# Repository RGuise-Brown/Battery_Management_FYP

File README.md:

# Battery Monitoring System for Lithium Thionyl Chloride Batteries

A battery monitoring system designed to track the health and state of charge of lithium thionyl chloride batteries operating in extreme cold conditions in the Southern Ocean Marginal Ice Zone (SO MIZ).

## Project Overview

This project was completed as a final year project (EEE4022S) for a Mechatronics Engineering degree at the University of Cape Town (UCT) in 2025.

**Author**: Rachael Guise-Brown  
**Supervisor**: Robyn Verrinder  
**Institution**: University of Cape Town

## Application

This battery monitoring system was designed for the **SHARC (Southern Hemisphere Antarctic Research Collective) Buoy**, which operates in the Southern Ocean Marginal Ice Zone. The system focuses on monitoring battery health in extreme cold conditions and adjusts the expected state of charge based on temperature changes.

## Battery Technology

Lithium thionyl chloride (Li-SOCl₂) batteries present unique monitoring challenges:
- **Primary battery** (non-rechargeable)
- **Very flat voltage discharge curve** - voltage alone is insufficient for accurate SOC estimation
- **Temperature-dependent performance** - capacity varies significantly with temperature

Due to these characteristics, the system uses **coulomb counting** and other methods to estimate state of charge, particularly important in the cold operating conditions of the Southern Ocean.

## System Features

### Hardware
- **INA226 Power Monitor**: Fully implemented and calibrated for accurate current and power measurement
- **BQ35100 Fuel Gauge**: Partial implementation but challenges with calibration and configuration without evaluation module (EVM)
- **Temperature Monitoring**: Three sensors tested
  - TMP117 digital I2C sensor
  - TMP36 (TO-92) analog sensor
  - TMP36 with shutdown (SOT-23) analog sensor (chosen sensor)
- **STM32 Nucleo-L4R5ZI**: Main microcontroller platform

### Firmware
- Real-time current, voltage, and capacity monitoring
- Temperature-compensated state of charge estimation
- Multiple algorithm implementations for data analysis
- I2C communication with all sensors
- Support for BQ35100 mode switching (EOS/ACC)
- Discharge cycle testing capabilities

## Repository Structure

```
├── firmware/          # Embedded C code for STM32
├── hardware/          # KiCad PCB designs and schematics
└── docs/              # Datasheets and reference documentation
```

## Implementation Status

### Fully Implemented ✓
- INA226 power monitor with calibration
- Temperature sensor array (TMP117, TMP36 sensors)
- BQ35100 basic functionality:
  - Current, voltage, and capacity reading
  - Mode switching (EOS ↔ ACC)
  - EOS impedance measurements (uncalibrated)
- Real-time monitoring algorithms
- Temperature-compensated SOC estimation

### Known Limitations
- BQ35100 I2C calibration is not functional through firmware

## Getting Started

### Hardware Setup
1. Review the hardware designs in `/hardware`
2. Assemble or obtain the custom PCBs:
   - BQ35100 fuel gauge board
   - Temperature sensor board
   - STM32 Nucleo Hat with INA226
3. Connect boards to STM32 Nucleo-L4R5ZI

### Firmware Setup
1. Navigate to `/firmware` directory
2. Build and flash the firmware to the STM32 Nucleo-L4R5ZI
3. Configure parameters as needed for your battery specifications

### Documentation
Refer to `/docs` for component datasheets and reference materials.

## Key Technologies

- **Microcontroller**: STM32L4R5ZI (ARM Cortex-M4)
- **Development Environment**: ARM GCC toolchain, STM32CubeIDE
- **Hardware Design**: KiCad
- **Communication Protocols**: I2C, UART
- **Programming Language**: C

## License

This project is licensed under the MIT License - see the LICENSE file for details.

## Acknowledgments

- **Robyn Verrinder** - Project supervisor
- **University of Cape Town** - Department of Electrical Engineering
- **SHARC Project** - Application context and requirements
- **Texas Instruments** - BQ35100 and INA226 reference designs

## Contact

Rachael Guise-Brown  
University of Cape Town  
2025

---

*Final Year Project (EEE4022S) - Mechatronics Engineering*  
*University of Cape Town*

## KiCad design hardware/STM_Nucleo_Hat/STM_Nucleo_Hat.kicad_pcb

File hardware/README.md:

# Hardware Documentation

Hardware design files for the Battery Monitoring System, including custom PCB designs created in KiCad.

## Overview

Three main PCB designs that integrate with an STM32 Nucleo-L4R5ZI development board to create a complete battery monitoring solution.

## PCB Designs

### 1. STM32 Nucleo Hat (STM_Nucleo_Hat)
Board borrowed from ARU that contains INA226 power monitor which is the only component used in this project.

**Files**: Located in `/STM_Nucleo_Hat/` directory

---

### 2. BQ35100 Board (FYP_PMIC)
Custom board featuring the Texas Instruments BQ35100 fuel gauge for battery monitoring.

**Files**: Located in `/FYP_PMIC/` directory

---

### 3. Temperature Sensor Board (FYP_temp)
Custom board with three temperature sensors:
- TMP117 (digital I2C sensor)
- TMP36 (TO-92 analog sensor)
- TMP36 with shutdown (SOT-23 analog sensor)

**Files**: Located in `/FYP_temp/` directory

---

## Schematics

Full schematics are provided in both PDF and image formats for easy viewing:

### BQ35100 Board
- `BQ35100 Schematic.pdf` - Full schematic documentation
- `BQ35100 Schematic.png` - Quick reference image

### INA226 Board
- `INA226 Full Board Schematic.pdf` - Complete board schematic
- `INA226 Schematic.jpeg` - Quick reference image

### Temperature Sensor Board
- `Temp Board Schematic.pdf` - Full schematic documentation
- `Temp Schematic.png` - Quick reference image

## KiCad Component Files

Custom component libraries and footprints are located in the `/KiCad component files/` directory. These include:
- Custom symbols for BQ35100, INA226, and temperature sensors

## Design Tools

**Software**: KiCad 6.0 or later

## Getting Started

Open the `.kicad_pro` file in the respective board directory, or view the PDF schematics directly.

## Component Information

**Key ICs Used**:
- INA226 power monitor (on STM Nucleo Hat)
- BQ35100 fuel gauge
- TMP117 digital temperature sensor
- TMP36 analog temperature sensors (x2)

**Microcontroller**: STM32 Nucleo-L4R5ZI development board

## Notes

- INA226 is fully implemented and calibrated
- BQ35100 has partial implementation (see firmware README for details)
- All designs created in KiCad

---

For firmware documentation, see the main repository README.

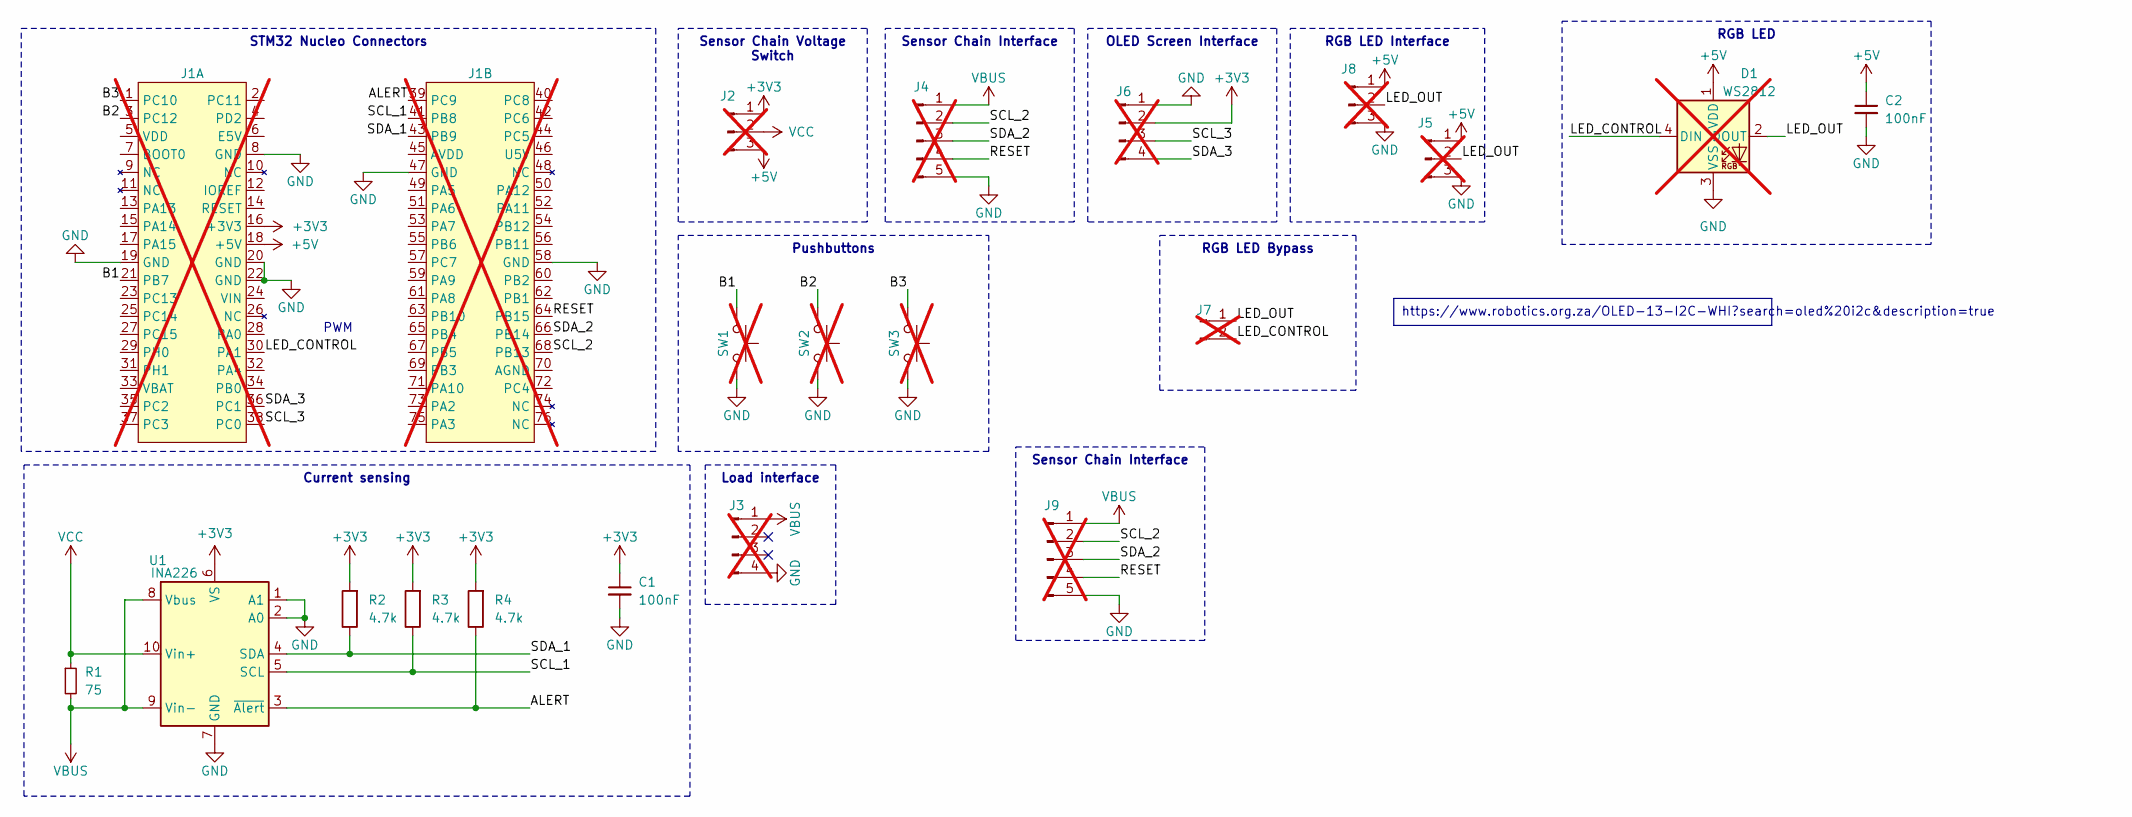
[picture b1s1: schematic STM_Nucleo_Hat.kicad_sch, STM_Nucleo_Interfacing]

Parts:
C1, C2: 100nF; C_0603_1608Metric; LCSC C14663
D1: WS2812; LED_WS2812B_PLCC4_5.0x5.0mm_P3.2mm; LCSC C2843785; not fitted
J1: Nucleo64-Pins; not fitted
J2, J5, J8: Conn_01x03_Pin; PinHeader_1x03_P2.54mm_Vertical; not fitted
J3: Conn_01x05_Pin; PinHeader_1x04_P2.54mm_Vertical; not fitted
J4, J9: Conn_01x05_Pin; PinHeader_1x05_P2.54mm_Vertical; not fitted
J6: Conn_01x05_Pin; 1.3_OLED_Screen; not fitted
J7: Conn_01x02_Pin; PinHeader_1x02_P2.54mm_Vertical; not fitted
R1: 75; C_0805_2012Metric_Pad1.18x1.45mm_HandSolder; LCSC C3033913
R2, R3, R4: 4.7k; R_0603_1608Metric; LCSC C23162
SW1, SW2, SW3: SW_Push; SW_PUSH_6mm; not fitted
U1: INA226; MSOP-10_3x3mm_P0.5mm; LCSC C49851

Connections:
+3V3: C1.1, J1.16 (+3V3), J2.1, J6.2, R2.2, R3.2, R4.2, U1.6 (VS)
+5V: C2.1, D1.1 (VDD), J1.18 (+5V), J2.3, J5.1, J8.1
/ALERT: J1.39 (PC9), R4.1, U1.3 (~Alert)
/B1: J1.21 (PB7), SW1.1
/B2: J1.3 (PC12), SW2.1
/B3: J1.1 (PC10), SW3.1
/LED_CONTROL: D1.4 (DIN), J1.30 (PA1), J7.2
/LED_OUT: D1.2 (DOUT), J5.2, J7.1, J8.2
/RESET: J1.64 (PB15), J4.4, J9.4
/SCL_1: J1.41 (PB8), R3.1, U1.5 (SCL)
/SCL_2: J1.68 (PB13), J4.2, J9.2
/SCL_3: J1.38 (PC0), J6.3
/SDA_1: J1.43 (PB9), R2.1, U1.4 (SDA)
/SDA_2: J1.66 (PB14), J4.3, J9.3
/SDA_3: J1.36 (PC1), J6.4
GND: C1.2, C2.2, D1.3 (VSS), J1.8 (GND), J1.19 (GND), J1.20 (GND), J1.22 (GND), J1.47 (GND), J1.58 (GND), J3.4, J4.5, J5.3, J6.1, J8.3, J9.5, SW1.2, SW2.2, SW3.2, U1.1 (A1), U1.2 (A0), U1.7 (GND)
VBUS: J3.1, J4.1, J9.1, R1.2, U1.8 (Vbus), U1.9 (Vin-)
VCC: J2.2, R1.1, U1.10 (Vin+)

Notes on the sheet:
Sensor Chain Interface
RGB LED
Pushbuttons
https://www.robotics.org.za/OLED-13-I2C-WHI?search=oled%20i2c&description=true
STM32 Nucleo Connectors
RGB LED Interface
Load interface
Current sensing
OLED Screen Interface
RGB LED Bypass
Sensor Chain Voltage Switch
PWM

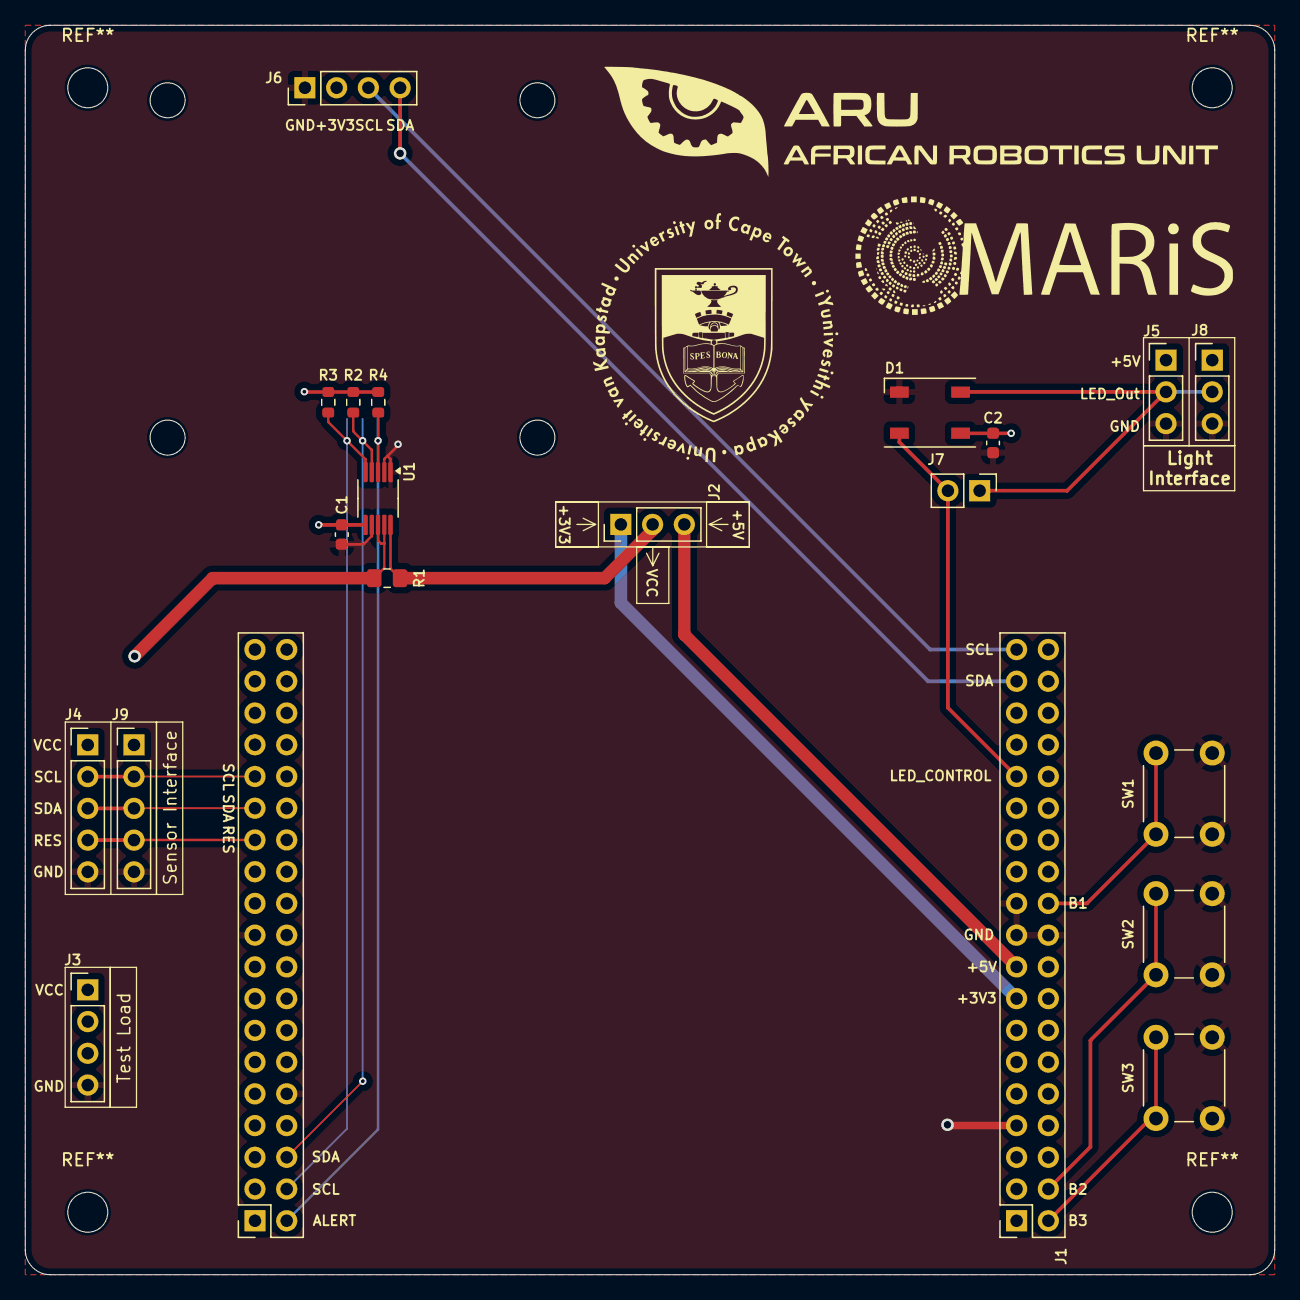
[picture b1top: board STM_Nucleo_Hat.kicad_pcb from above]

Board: 4 copper layers, 100.0 x 100.0 mm, 20 parts (0 on the bottom side), 18 nets.

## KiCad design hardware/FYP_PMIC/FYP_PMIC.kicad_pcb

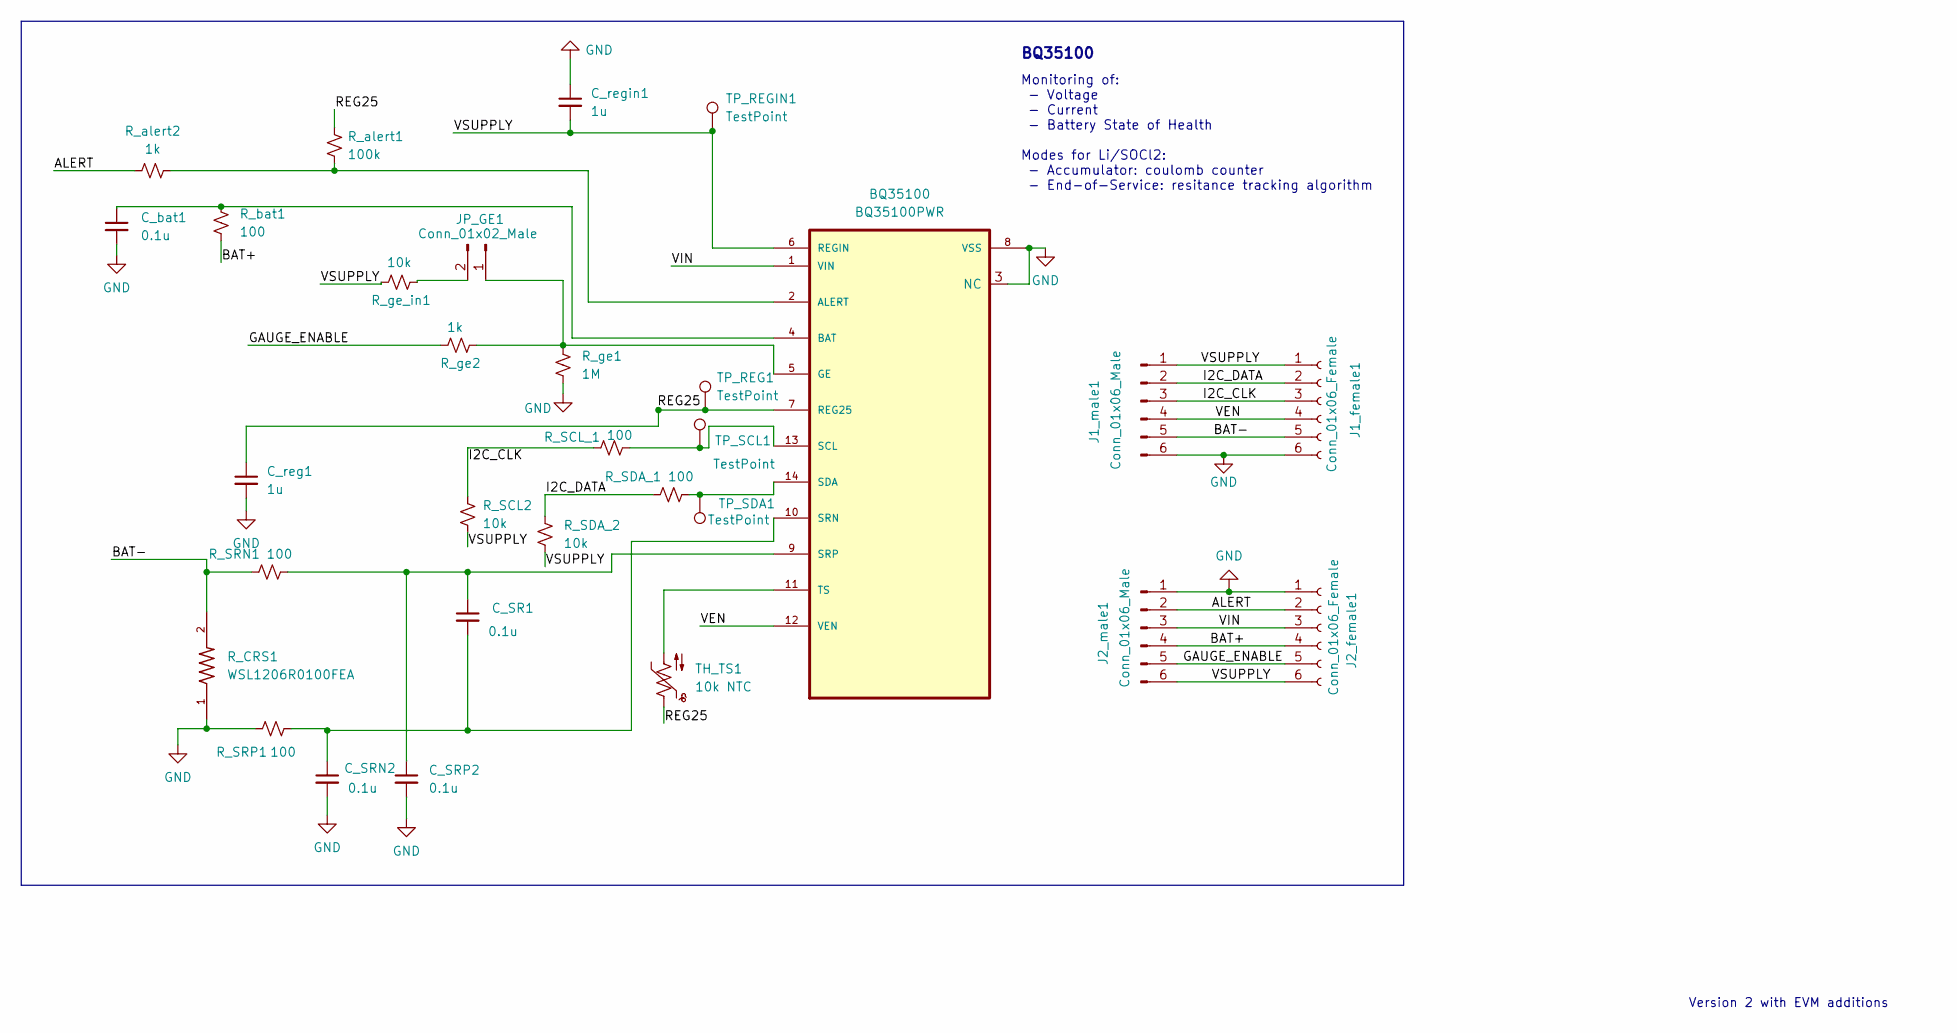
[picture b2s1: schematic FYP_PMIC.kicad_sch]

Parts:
BQ35100: BQ35100PWR; SOP65P640X120-14N; DigiKey_Part_Number 296-47251-1-ND
C_SR1: 0.1u; C_0402_1005Metric
C_SRN2: 0.1u; C_0402_1005Metric
C_SRP2: 0.1u; C_0402_1005Metric
C_bat1: 0.1u; C_0402_1005Metric
C_reg1: 1u; C_0603_1608Metric
C_regin1: 1u; C_0603_1608Metric
J1_female1, J2_female1: Conn_01x06_Female; PinSocket_1x06_P2.54mm_Vertical
J1_male1, J2_male1: Conn_01x06_Male; PinHeader_1x06_P2.54mm_Vertical
JP_GE1: Conn_01x02_Male; PinHeader_1x02_P2.54mm_Vertical
R_CRS1: WSL1206R0100FEA; RESC3216X90
R_SCL2: 10k; R_0805_2012Metric
R_SCL_1: 100; R_0805_2012Metric
R_SDA_1: 100; R_0805_2012Metric
R_SDA_2: 10k; R_0805_2012Metric
R_SRN1: 100; R_0805_2012Metric
R_SRP1: 100; R_0805_2012Metric
R_alert1: 100k; R_1206_3216Metric
R_alert2: 1k; R_1206_3216Metric
R_bat1: 100; R_0805_2012Metric
R_ge1: 1M; R_1206_3216Metric
R_ge2: 1k; R_1206_3216Metric
R_ge_in1: 10k; R_0805_2012Metric
TH_TS1: 10k NTC; C_Disc_D5.0mm_W2.5mm_P2.50mm
TP_REG1: TestPoint; TestPoint_Pad_D2.0mm
TP_REGIN1: TestPoint; TestPoint_Pad_D2.0mm
TP_SCL1: TestPoint; TestPoint_Pad_D2.0mm
TP_SDA1: TestPoint; TestPoint_Pad_D2.0mm

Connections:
/ALERT: J2_female1.2, J2_male1.2, R_alert2.1
/BAT+: J2_female1.4, J2_male1.4, R_bat1.2
/BAT-: J1_female1.5, J1_male1.5, R_CRS1.2, R_SRN1.1
/GAUGE_ENABLE: J2_female1.5, J2_male1.5, R_ge2.1
/I2C_CLK: J1_female1.3, J1_male1.3, R_SCL2.1, R_SCL_1.1
/I2C_DATA: J1_female1.2, J1_male1.2, R_SDA_1.1, R_SDA_2.1
/REG25: BQ35100.7 (REG25), C_reg1.1, R_alert1.1, TH_TS1.1, TP_REG1.1
/VEN: BQ35100.12 (VEN), J1_female1.4, J1_male1.4
/VIN: BQ35100.1 (VIN), J2_female1.3, J2_male1.3
/VSUPPLY: BQ35100.6 (REGIN), C_regin1.2, J1_female1.1, J1_male1.1, J2_female1.6, J2_male1.6, R_SCL2.2, R_SDA_2.2, R_ge_in1.1, TP_REGIN1.1
GND: BQ35100.3 (NC), BQ35100.8 (VSS), C_SRN2.2, C_SRP2.2, C_bat1.2, C_reg1.2, C_regin1.1, J1_female1.6, J1_male1.6, J2_female1.1, J2_male1.1, R_CRS1.1, R_SRP1.1, R_ge1.2
unnamed: BQ35100.2 (ALERT), R_alert1.2, R_alert2.2
unnamed: BQ35100.4 (BAT), C_bat1.1, R_bat1.1
unnamed: BQ35100.5 (GE), JP_GE1.1, R_ge1.1, R_ge2.2
unnamed: BQ35100.9 (SRP), C_SR1.1, C_SRP2.1, R_SRN1.2
unnamed: BQ35100.10 (SRN), C_SR1.2, C_SRN2.1, R_SRP1.2
unnamed: BQ35100.11 (TS), TH_TS1.2
unnamed: BQ35100.13 (SCL), R_SCL_1.2, TP_SCL1.1
unnamed: BQ35100.14 (SDA), R_SDA_1.2, TP_SDA1.1
unnamed: JP_GE1.2, R_ge_in1.2

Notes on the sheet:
BQ35100
Version 2 with EVM additions
Monitoring of: - Voltage - Current - Battery State of Health Modes for Li/SOCl2: - Accumulator: coulomb counter - End-of-Service: resitance tracking algorithm

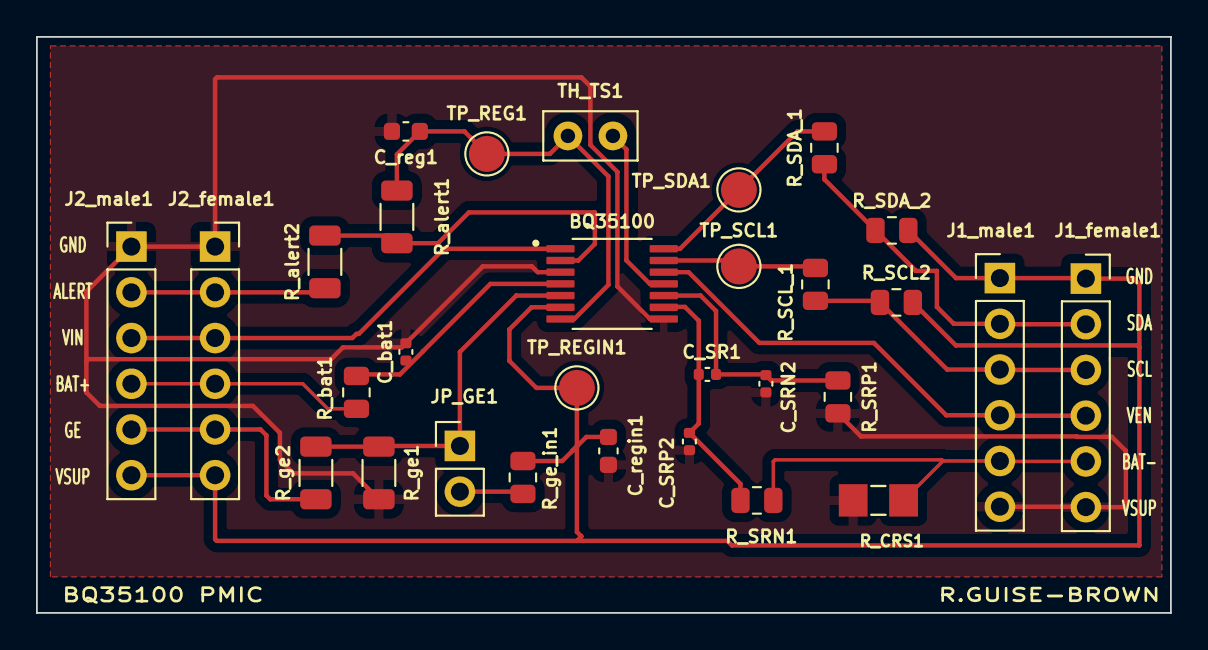
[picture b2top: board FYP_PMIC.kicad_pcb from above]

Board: 2 copper layers, 63.0 x 32.0 mm, 30 parts (0 on the bottom side), 20 nets.

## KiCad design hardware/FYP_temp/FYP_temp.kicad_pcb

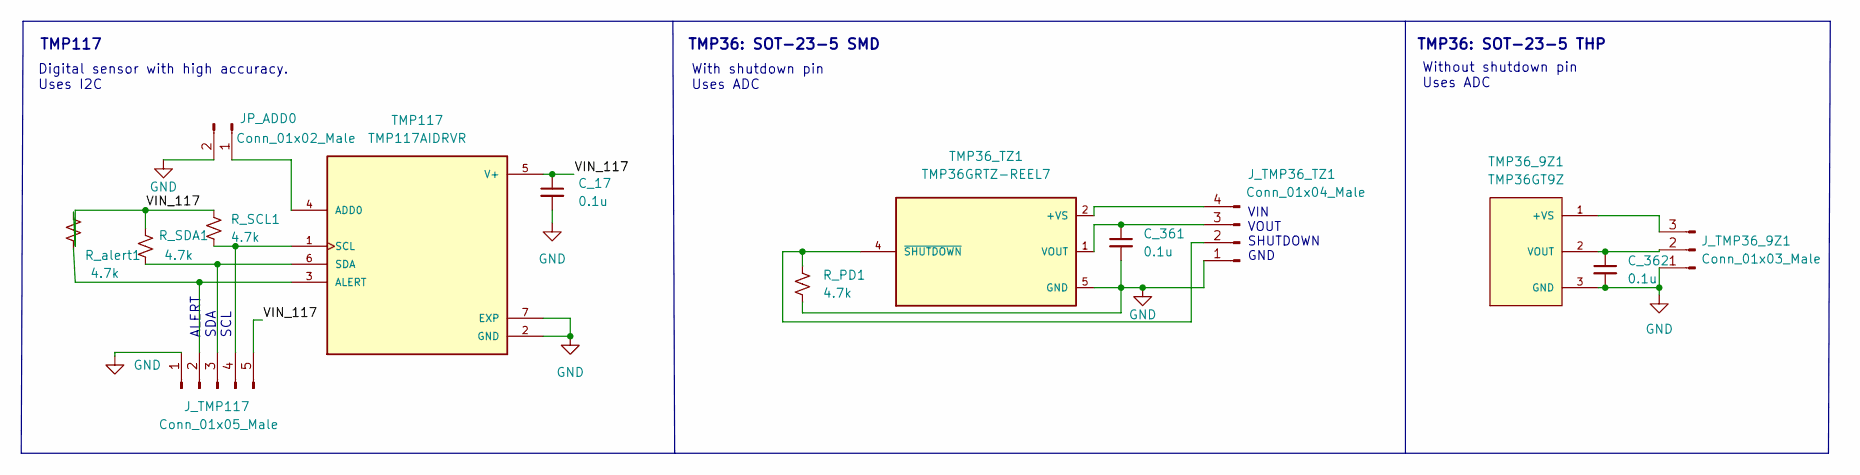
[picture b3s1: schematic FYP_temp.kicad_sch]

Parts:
C_17, C_361, C_362: 0.1u; C_0402_1005Metric
JP_ADD0: Conn_01x02_Male; PinHeader_1x02_P2.54mm_Vertical
J_TMP36_9Z1: Conn_01x03_Male; PinHeader_1x03_P2.54mm_Vertical
J_TMP36_TZ1: Conn_01x04_Male; PinHeader_1x04_P2.54mm_Vertical
J_TMP117: Conn_01x05_Male; PinHeader_1x05_P2.54mm_Vertical
R_PD1: 4.7k; R_0603_1608Metric
R_SCL1: 4.7k; R_0603_1608Metric
R_SDA1: 4.7k; R_0603_1608Metric
R_alert1: 4.7k; R_0603_1608Metric
TMP36_9Z1: TMP36GT9Z; TO92127P521H733-3; PARTREV H
TMP36_TZ1: TMP36GRTZ-REEL7; SOT95P280X145-5N; PARTREV H
TMP117: TMP117AIDRVR; SON65P200X200X80-7N; PARTREV B

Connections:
/VIN_117: C_17.1, J_TMP117.5, R_SCL1.1, R_SDA1.1, R_alert1.1, TMP117.5 (V+)
GND: C_17.2, C_361.2, C_362.2, JP_ADD0.2, J_TMP36_9Z1.1, J_TMP36_TZ1.1, J_TMP117.1, R_PD1.2, TMP36_9Z1.3 (GND), TMP36_TZ1.5 (GND), TMP117.2 (GND), TMP117.7 (EXP)
unnamed: C_361.1, J_TMP36_TZ1.3, TMP36_TZ1.1 (VOUT)
unnamed: C_362.1, J_TMP36_9Z1.2, TMP36_9Z1.2 (VOUT)
unnamed: JP_ADD0.1, TMP117.4 (ADD0)
unnamed: J_TMP36_9Z1.3, TMP36_9Z1.1 (+VS)
unnamed: J_TMP36_TZ1.2, R_PD1.1, TMP36_TZ1.4 (~SHUTDOWN)
unnamed: J_TMP36_TZ1.4, TMP36_TZ1.2 (+VS)
unnamed: J_TMP117.2, R_alert1.2, TMP117.3 (ALERT)
unnamed: J_TMP117.3, R_SDA1.2, TMP117.6 (SDA)
unnamed: J_TMP117.4, R_SCL1.2, TMP117.1 (SCL)

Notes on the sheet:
Without shutdown pin Uses ADC
Digital sensor with high accuracy. Uses I2C
TMP36: SOT-23-5 THP
TMP36: SOT-23-5 SMD
VIN VOUT SHUTDOWN GND
ALERT SDA SCL
With shutdown pin Uses ADC
TMP117

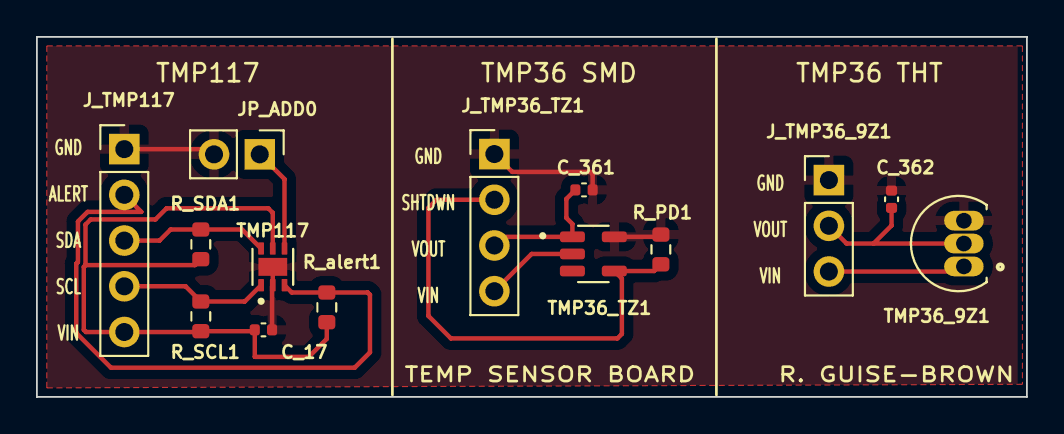
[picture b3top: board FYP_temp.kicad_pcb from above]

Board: 2 copper layers, 55.0 x 20.0 mm, 14 parts (0 on the bottom side), 11 nets.

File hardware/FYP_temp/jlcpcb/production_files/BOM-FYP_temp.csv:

Comment,Designator,Footprint,LCSC
0.1u,"C_17,C_361,C_362",C_0402_1005Metric,C1525
4.7k,"R_PD1,R_SCL1,R_SDA1,R_alert1",R_0603_1608Metric,C23162
TMP36GT9Z,TMP36_9Z1,TO92127P521H733-3,C5692995
TMP36GRTZ-REEL7,TMP36_TZ1,SOT95P280X145-5N,C5692996
TMP117AIDRVR,TMP117,SON65P200X200X80-7N,C699536
Conn_01x04_Male,J_TMP36_TZ1,PinHeader_1x04_P2.54mm_Vertical,
Conn_01x02_Male,JP_ADD0,PinHeader_1x02_P2.54mm_Vertical,
Conn_01x05_Male,J_TMP117,PinHeader_1x05_P2.54mm_Vertical,
Conn_01x03_Male,J_TMP36_9Z1,PinHeader_1x03_P2.54mm_Vertical,

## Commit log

2025-09-26 Datasheets
2025-09-26 Memory mapping zipped PDF
2025-09-26 LED, UART and ADC
2025-09-26 temp sensor enable
2025-09-28 I2C with temp sensor intial communication
2025-09-28 I2C with temperature readings working + debugging
2025-09-28 All temp sensors working with main.c code
2025-09-29 new file name for i2c_temp
2025-10-10 BQ35100 code for EOS and ACC Mode
2025-10-10 Battery monitoring combined
2025-10-13 BMS full algorithm and battery monitoring
2025-10-15 algorithms,full testing, reduced, 226
2025-10-29 last updates
2025-10-29 Add .DS_Store to gitignore
2025-10-29 KiCad component files
2025-10-29 KiCad Temp PCB
2025-10-29 KiCad BQ35100 board
2025-10-29 KiCAD INA226 board
2025-10-29 Schematics
2025-10-29 STM32 User manual
